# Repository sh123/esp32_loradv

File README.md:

# ESP32 Codec2/OPUS DV Handheld Transceiver

## Introduction
⚠ **Please note that this device is experimental and lacks any form of certification. The author holds no responsibility for any fines incurred due to spectrum misuse, legal violations, or damages caused during its use. As with any experimental project, it is essential that you fully understand what you are doing and use it at your own risk.**

This project is a hobby/amateur/toy/educational radio ESP32 based LoRa/FSK Codec2/OPUS DV 3d printed handheld trasceiver a.k.a. walkie-talkie, which is using 1W/2W `E22-400M30S/E22-400M33S` (SX1268) radio module (UHF, 70cm band) or optionally 100mW `RA-01/RA-02` (SX1278) module. 

In theory, it could also be used with other modules from `E22-xxxMxxS` series with compatible pinouts, but targetting other bands, such as `E22-868M30S/E22-900M30S` (SX1262) modules (UHF, 868/915 MHz) or `E22-170M33S`/`E22-220M30S`, but not tested.

It functions like a standard FM walkie-talkie and, for simplicity and traffic optimization, does not utilize any communication protocol. Instead, it transmits audio codec frames (DV) using pre-configured digital radio modulation, such as LoRA or FSK. There are ideas to add voice over AX.25 and perhaps M17 protocol support in the future.

Overall components cost for this project is about 15-20$.

Schematics for the new board design, which includes integrated components, can be found in the `extras/schematics` directory. The pinouts remain compatible with the first prototype version. While there is a designated space for a GPS module, it should not be soldered as it is not currently supported; it is included solely for potential future experiments.

First prototype is based on https://github.com/sh123/esp32_loraprs modem, but uses additional peripherals:
- I2S speaker module MAX98357A + 4-8ohm 3w speaker (40mm diameter)
- I2S microphone INMP441
- PTT button (new board uses right angeled push button)
- Rotary encoder with push button (new board uses EC11 right angeled encoder)
- Small OLED display SSD1306 128x32
- Battery voltage monitoring (just voltage divider fed into ADC pin, see schematics)
- Powered from a single commonly avaialble 18650 cell (for example from old laptop battery)
- Uses combined charge + 5v boost controller based on Hotchip HT4928S (it is usually used in low capacity single cell USB power banks), but **better to use controllers such as IP5305_SK or similar without auto shutdown on low current!**.

Supports next features:
- Supports LoRa and FSK (no FEC) modulation with configurable modulation parameters from settings
- Supports Codec2 (low bit rate, 700-3200 bps) and OPUS (medium/high bit rate, 2400-512000 bps) audio codecs, codec could be selected from settings
- Goes into ESP32 light sleep when no activity, so all power consumption is around 30-40mA when in sleep RX (even lower with built-in esp32 leds scrapped), wakes up on new data from radio module or when user starts transmitting, consumes about 90-100mA in active receive and about 700-800mA in full power 1W transmit, so single 18650 cell should last for about 48 hours when in idle RX
- Settings menu on long encoder button click, allows to change frequency and other parameters
- Output power tunable from settings from ~1mW (for ISM toy usage) up to 2W (for amateur radio experiments)
- Experimental no warranty privacy option for ISM low power usage (⚠ **check your country regulations if it is allowed by the ISM band plan before experimenting as it might be illegal in some countries**), it is based on [ChaCha20-Poly1305](https://en.wikipedia.org/wiki/ChaCha20-Poly1305) stream cypher provided by [rwheater/Crypto](https://github.com/rweather/arduinolibs) library, it is comparable to AES256, uses 256 bits key, provides message authentication, but should have lower CPU requirements and power usage.

Planned features/ideas:
- Frequency split repeater mode, where two transceivers will be linked using espnow, so one will receive voice on RX frequency and then send packet using espnow to second transmitter which will receive packet using espnow and re-transmit it on TX frequency, this way receiver and transmitter could be positioned further apart with separate antennas thus eliminating need for duplexer
- Bluetooth headset pairing to use with hands free, so can use headset instead of i2s speaker/mic when needed
- Voice over AX.25, so meta data such as callsign could be included and visible on the other end
- M17 protocol support

## Build instructions
- Modify `include/config.h` if needed
- Install platformio
- Build with platformio
- Upload with platformio

## BOM
Bill of materials (BOM) for the new board constuction (credits to n0p and his club members for collecting it)
```
ESP-WROOM32 30pin - https://es.aliexpress.com/item/1005005953505528.html
Modem LoRa E22-400M30S (SX1268) - https://es.aliexpress.com/item/1005003122961059.html
I2S speaker module MAX98357A - https://es.aliexpress.com/item/1005005383121121.html
4ohm 3w speaker (40mm diameter) - https://es.aliexpress.com/item/1005006684947554.html
I2S microphone INMP441 - https://es.aliexpress.com/item/1005007889064664.html
Rotary encoder with push button - https://es.aliexpress.com/item/1005008091948369.html 
Small OLED display SSD1306 128×32 - https://es.aliexpress.com/item/1005008096924594.html
Uses combined charge + 5v boost controller - https://es.aliexpress.com/item/1005008657948784.html

18650 Cell
Botón switch tactile SKHH angled - https://es.aliexpress.com/item/1005005369415986.html
SMA-J-P-X-ST-EM1 Edgemount - https://es.aliexpress.com/item/10000000835065.html
R1 - 100k 0603 - https://es.aliexpress.com/item/1005005677654015.html
R2-R7 - 10k 0603 - https://es.aliexpress.com/item/1005005677654015.html
C1, C3-C8, C10, C11 - 100nF 0603 - https://es.aliexpress.com/item/32371454429.html
C2 - Elec 100uF SMD 3×5,3 - https://es.aliexpress.com/item/1005006724593986.html
C9 - 47uF Radial D4 mm P2 mm - https://es.aliexpress.com/item/1005005022177024.html

GPS - OPTIONAL - UNSUPPORTED ON WALKIE FW - CONFLICTS WITH ON BOARD SERIAL PORT PROGRAMMER - https://es.aliexpress.com/item/1005008733474270.html
```

## Pictures

Two fully 3d printed prototypes were built based on `esp32_loraprs` modem board.

List of peripherals used.

New board design with all components integrated into the board (except battery and charging circuit).

Case for the new board version with battery compartment.

Assembled board with new design.

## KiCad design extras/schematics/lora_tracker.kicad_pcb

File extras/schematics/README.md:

# ESP32 DV transceiver board

This is transceiver board for ESP32 DV handheld transceiver with integrated modules, except battery and charge controller.

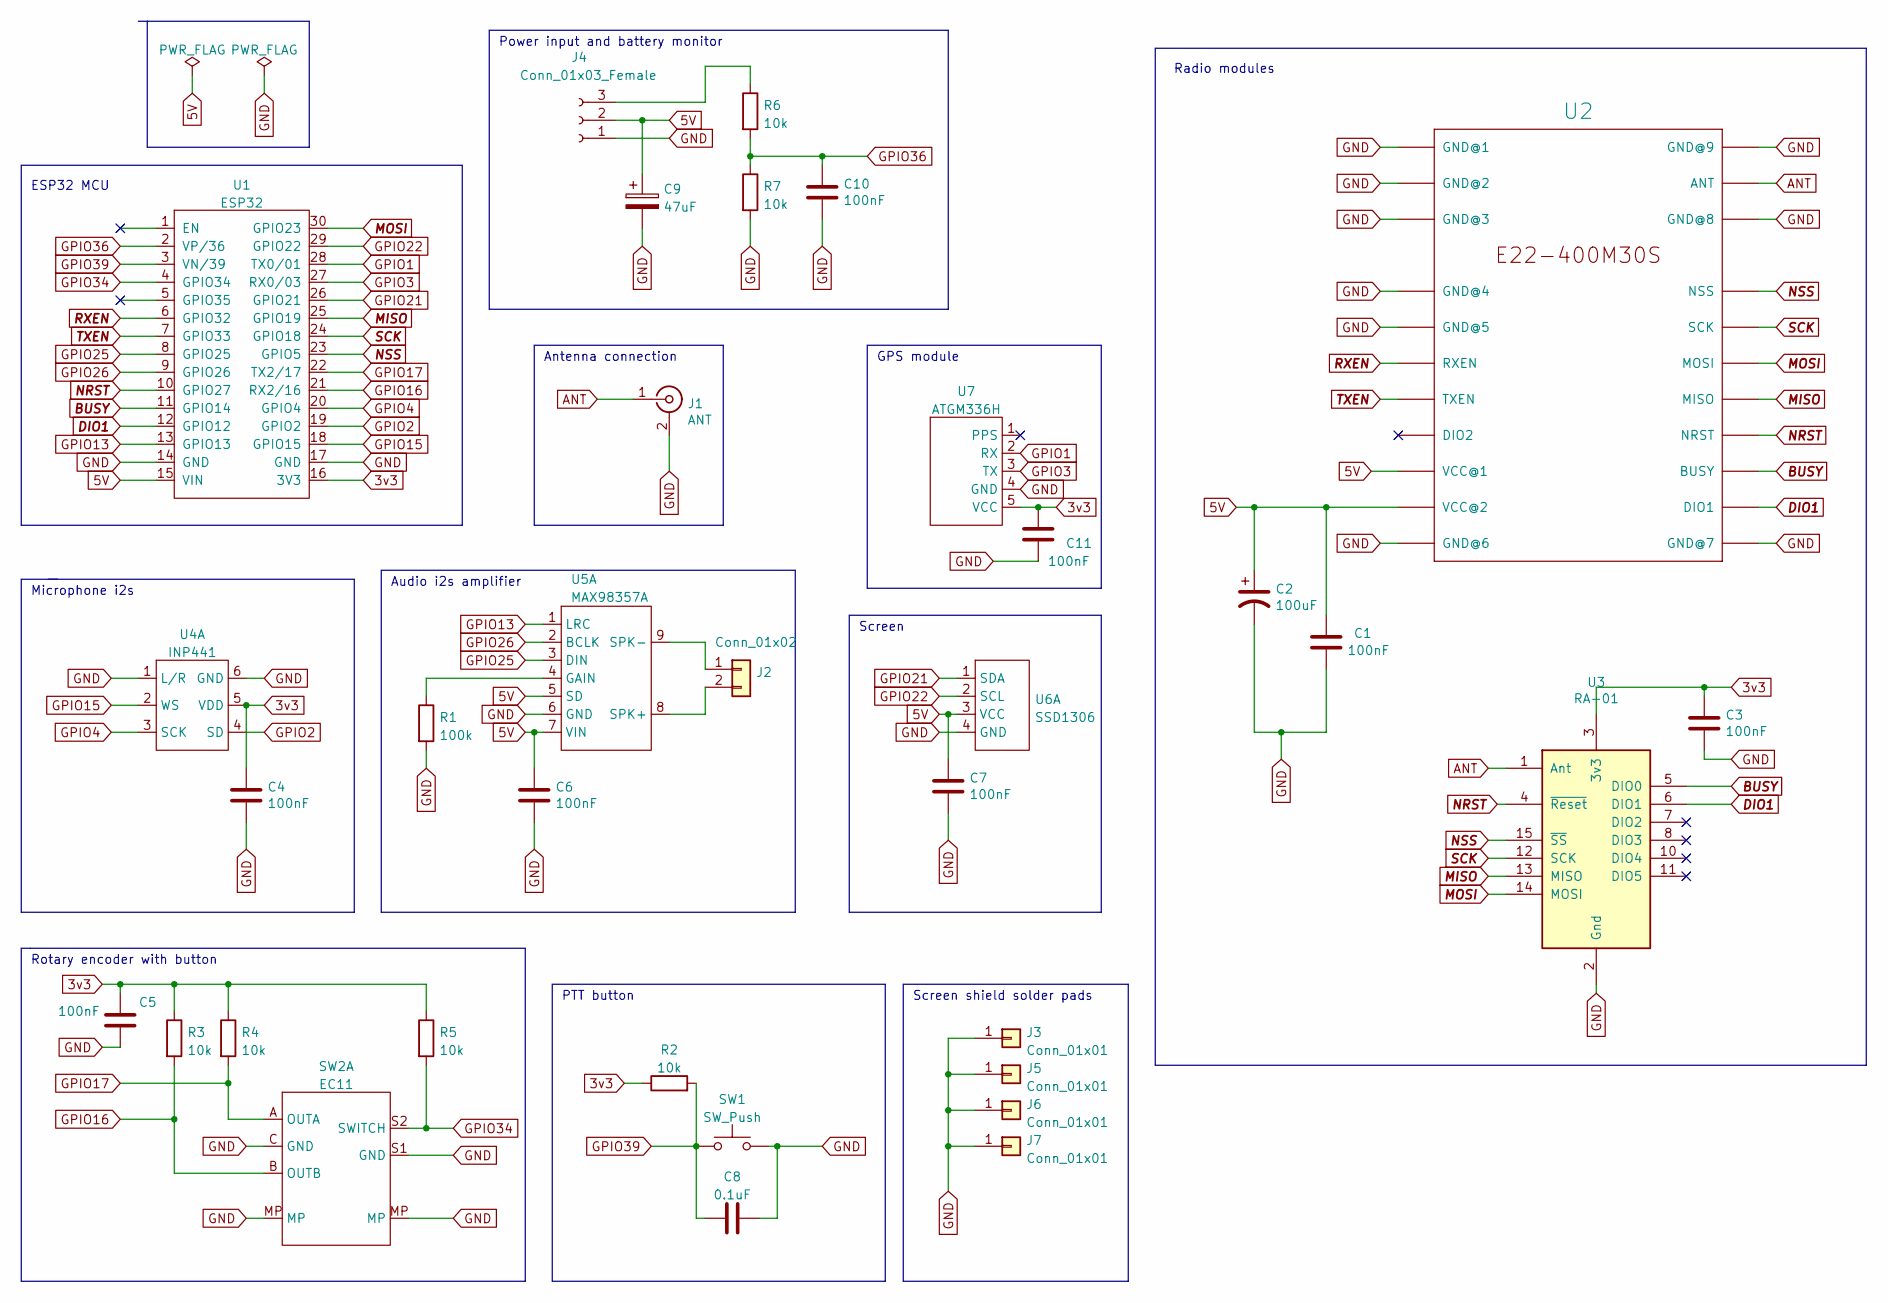
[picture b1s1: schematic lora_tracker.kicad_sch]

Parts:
C1, C3, C4, C5, C6, C7, C10, C11: 100nF; C_0603_1608Metric_Pad1.08x0.95mm_HandSolder
C2: 100uF; CP_Elec_3x5.3
C8: 0.1uF; C_0603_1608Metric_Pad1.08x0.95mm_HandSolder
C9: 47uF; CP_Radial_D4.0mm_P2.00mm
J1: ANT; SMA_Samtec_SMA-J-P-X-ST-EM1_EdgeMount
J2: Conn_01x02; PinHeader_2x01_P2.54mm_Vertical_SMD
J3, J5, J6, J7: Conn_01x01; TestPoint_Pad_1.5x1.5mm
J4: Conn_01x03_Female; PinHeader_1x03_P2.54mm_Vertical
R1: 100k; R_0603_1608Metric_Pad0.98x0.95mm_HandSolder
R2, R3, R4, R5, R6, R7: 10k; R_0603_1608Metric_Pad0.98x0.95mm_HandSolder
SW1: SW_Push; SW_Tactile_SKHH_Angled
SW2: EC11; ec11
U1: ESP32; esp32-devkit-wide_30pin
U2: E22-400M30S
U3: RA-01; Ai-Thinker-Ra-01-LoRa
U4: INP441; inp441
U5: MAX98357A
U6: SSD1306
U7: ATGM336H

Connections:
3v3: C3.1, C4.1, C5.1, C11.1, R2.1, R3.1, R4.1, R5.1, U1.16 (3V3), U3.3 (3v3), U4.5 (VDD), U7.5 (VCC)
5V: C1.1, C2.1, C6.1, C7.1, C9.1, J4.2, U1.15 (VIN), U2.9 (VCC@1), U2.10 (VCC@2), U5.5 (SD), U5.7 (VIN), U6.3 (VCC)
ANT: J1.1 (In), U2.21 (ANT), U3.1 (Ant)
BUSY: U1.11 (GPIO14), U2.14 (BUSY), U3.5 (DIO0)
DIO1: U1.12 (GPIO12), U2.13 (DIO1), U3.6 (DIO1)
GND: C1.2, C2.2, C3.2, C4.2, C5.2, C6.2, C7.2, C8.2, C9.2, C10.2, C11.2, J1.2 (Ext), J3.1, J4.1, J5.1, J6.1, J7.1, R1.2, R7.2, SW1.2, SW2.C (GND), SW2.MP, SW2.S1 (GND), U1.14 (GND), U1.17 (GND), U2.1 (GND@1), U2.2 (GND@2), U2.3 (GND@3), U2.4 (GND@4), U2.5 (GND@5), U2.11 (GND@6), U2.12 (GND@7), U2.20 (GND@8), U2.22 (GND@9), U3.2 (Gnd), U3.9 (Gnd), U3.16 (Gnd), U4.1 (L/R), U4.6 (GND), U5.6 (GND), U6.4 (GND), U7.4 (GND)
GPIO1: U1.28 (TX0/01), U7.2 (RX)
GPIO2: U1.19 (GPIO2), U4.4 (SD)
GPIO3: U1.27 (RX0/03), U7.3 (TX)
GPIO4: U1.20 (GPIO4), U4.3 (SCK)
GPIO13: U1.13 (GPIO13), U5.1 (LRC)
GPIO15: U1.18 (GPIO15), U4.2 (WS)
GPIO16: R3.2, SW2.B (OUTB), U1.21 (RX2/16)
GPIO17: R4.2, SW2.A (OUTA), U1.22 (TX2/17)
GPIO21: U1.26 (GPIO21), U6.1 (SDA)
GPIO22: U1.29 (GPIO22), U6.2 (SCL)
GPIO25: U1.8 (GPIO25), U5.3 (DIN)
GPIO26: U1.9 (GPIO26), U5.2 (BCLK)
GPIO34: R5.2, SW2.S2 (SWITCH), U1.4 (GPIO34)
GPIO36: C10.1, R6.2, R7.1, U1.2 (VP/36)
GPIO39: C8.1, R2.2, SW1.1, U1.3 (VN/39)
MISO: U1.25 (GPIO19), U2.16 (MISO), U3.13 (MISO)
MOSI: U1.30 (GPIO23), U2.17 (MOSI), U3.14 (MOSI)
NRST: U1.10 (GPIO27), U2.15 (NRST), U3.4 (~Reset)
NSS: U1.23 (GPIO5), U2.19 (NSS), U3.15 (~SS)
unnamed: J2.1, U5.9 (SPK-)
unnamed: J2.2, U5.8 (SPK+)
unnamed: J4.3, R6.1
unnamed: R1.1, U5.4 (GAIN)
RXEN: U1.6 (GPIO32), U2.6 (RXEN)
SCK: U1.24 (GPIO18), U2.18 (SCK), U3.12 (SCK)
TXEN: U1.7 (GPIO33), U2.7 (TXEN)

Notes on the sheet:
Antenna connection
Microphone i2s
Audio i2s amplifier
GPS module
Screen shield solder pads
Radio modules
PTT button
Power input and battery monitor
Screen
ESP32 MCU
Rotary encoder with button

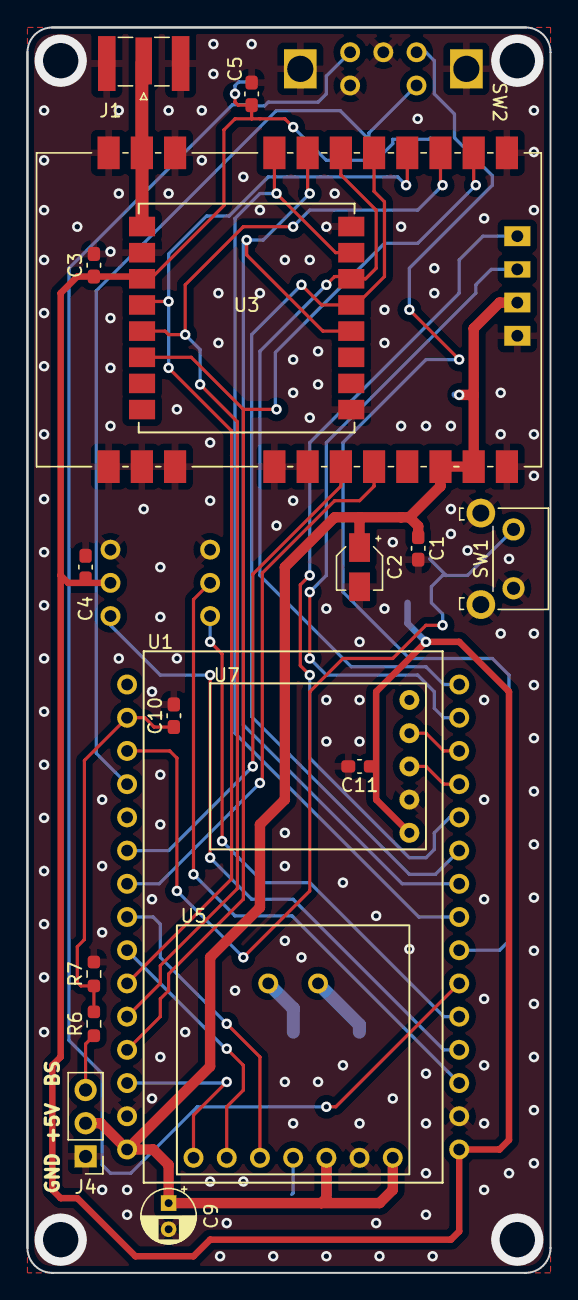
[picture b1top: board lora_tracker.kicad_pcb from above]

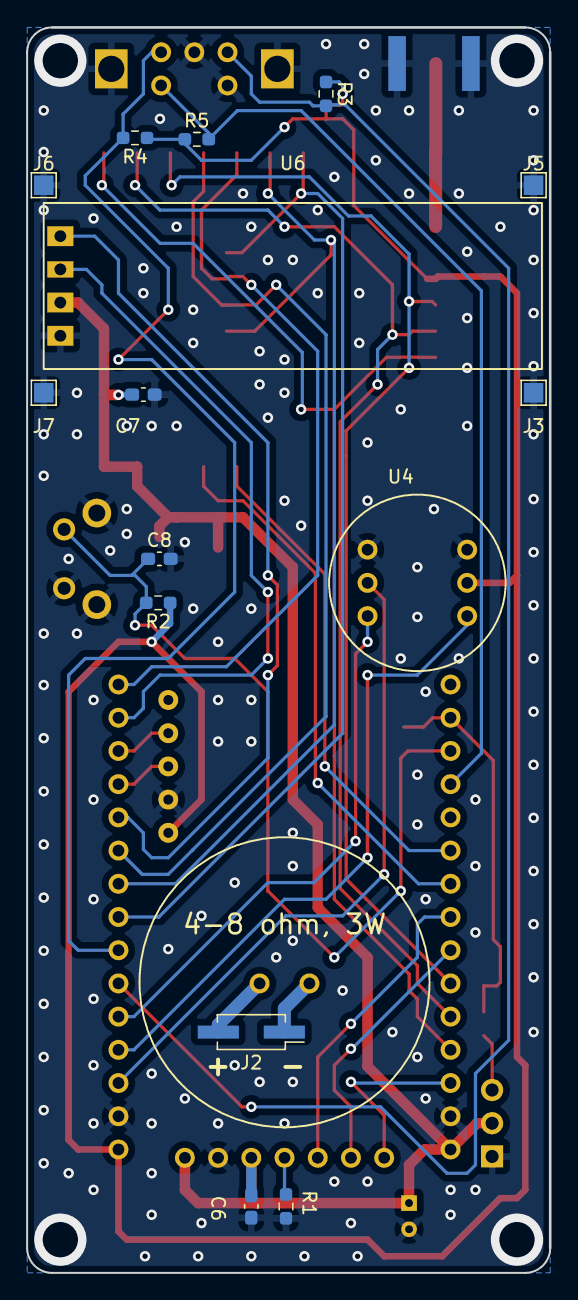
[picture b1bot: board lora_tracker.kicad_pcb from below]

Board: 2 copper layers, 40.0 x 95.2 mm, 34 parts (15 on the bottom side), 32 nets.

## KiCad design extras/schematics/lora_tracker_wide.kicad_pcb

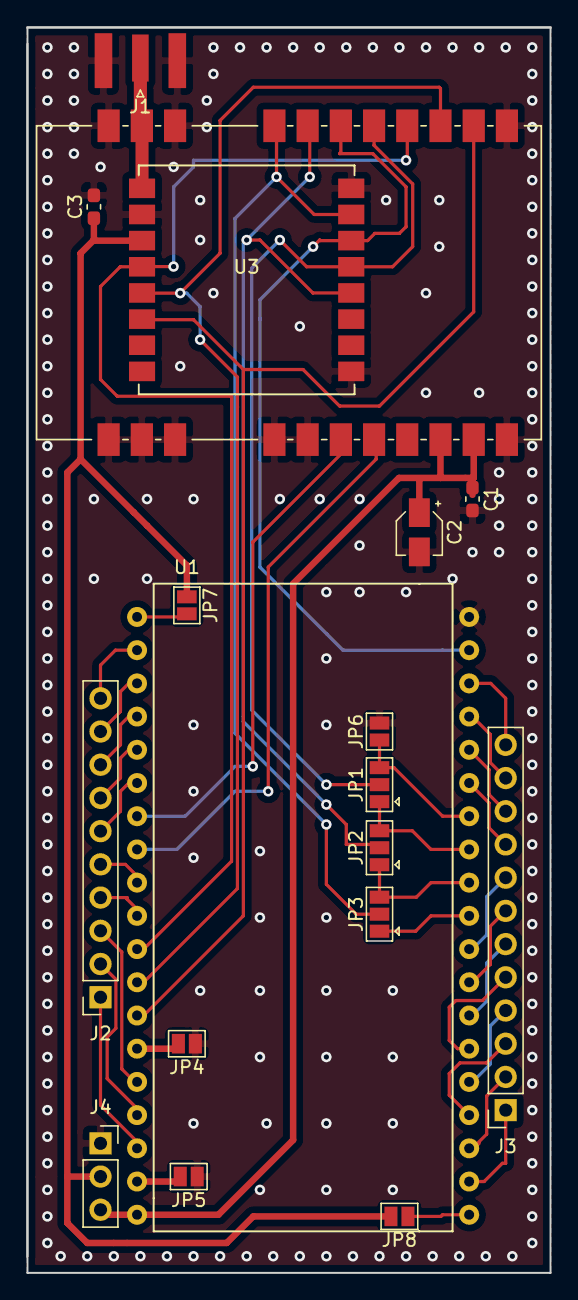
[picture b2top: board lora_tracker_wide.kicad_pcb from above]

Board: 2 copper layers, 40.0 x 95.2 mm, 18 parts (0 on the bottom side), 43 nets.

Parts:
C1, C3: 100nF; C_0603_1608Metric_Pad1.05x0.95mm_HandSolder
C2: 100uF; CP_Elec_3x5.3
J1: Conn_Coaxial; SMA_Samtec_SMA-J-P-H-ST-EM1_EdgeMount
J2: Conn_01x10_Female; PinSocket_1x10_P2.54mm_Vertical
J3: Conn_01x12_Female; PinSocket_1x12_P2.54mm_Vertical
J4: Conn_01x03_Female; PinSocket_1x03_P2.54mm_Vertical
JP1, JP2, JP3: SolderJumper_3_Open; SolderJumper-3_P1.3mm_Open_Pad1.0x1.5mm
JP4, JP5, JP6, JP7, JP8: SolderJumper_2_Open; SolderJumper-2_P1.3mm_Open_Pad1.0x1.5mm
U1: ESP32; esp32-devkit-wide
U2: E22-400M30S
U3: Ai-Thinker-Ra-01; Ai-Thinker-Ra-01-LoRa

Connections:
3v3: C3.1, J4.2, JP7.1, JP8.2, U3.3
BUSY: U1.12, U2.14, U3.5
DIO1: U1.13, U2.13, U3.6
EN: J2.10, U1.2
GND: C1.2, C2.2, C3.2, J1.2, J4.1, JP4.1, JP5.1, JP6.2, U1.38, U2.1, U2.2, U2.3, U2.4, U2.5, U2.11, U2.12, U2.20, U2.22, U3.2, U3.9, U3.16
GPIO0: J3.5, U1.25
GPIO1: J3.11, U1.35
GPIO2: J3.4, U1.24
GPIO3: J3.10, U1.34
GPIO4: J3.6, U1.26
GPIO7: J3.1, U1.21
GPIO8: J3.2, U1.22
GPIO9: J2.2, U1.16
GPIO10: J2.1, U1.17
GPIO13: J2.3, U1.15
GPIO15: J3.3, U1.23
GPIO16: J3.7, U1.27
GPIO17: J3.8, U1.28
GPIO21: J3.9, U1.33
GPIO22: J3.12, U1.36
GPIO25: J2.5, U1.9
GPIO26: J2.4, U1.10
GPIO34: J2.7, U1.5
GPIO35: J2.6, U1.6
GPIO36: J2.9, U1.3
GPIO39: J2.8, U1.4
MISO: JP1.2, U2.16, U3.13
MOSI: U1.37, U2.17, U3.14
NRST: U1.11, U2.15, U3.4
NSS: JP3.2, U2.19, U3.15
unnamed: J1.1, U2.21, U3.1
unnamed: JP1.1, JP2.3, U1.31
unnamed: JP1.3, JP6.1, U1.32
unnamed: JP2.1, JP3.3, U1.30
unnamed: JP3.1, U1.29
unnamed: JP4.2, U1.14
unnamed: JP5.2, U1.18
unnamed: JP7.2, U1.1
unnamed: JP8.1, U1.20
RXEN: U1.7, U2.6
SCK: JP2.2, U2.18, U3.12
TXEN: U1.8, U2.7
VCC: C1.1, C2.1, J4.3, U1.19, U2.9, U2.10

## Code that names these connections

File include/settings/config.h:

#ifndef LORADV_CONFIG_H
#define LORADV_CONFIG_H

#include <Arduino.h>
#include <Preferences.h>

#define DEBUGLOG_DEFAULT_LOG_LEVEL_INFO
#include <DebugLog.h>

#include "version.h"
#include "settings/default_config.h"

namespace LoraDv {

class Config {
public:
  int Version;          // config version

  DebugLogLevel LogLevel;    // log level

  // modulation type
  int ModType;          // 0 - lora, 1 - fsk

  // lora modulation parameters
  long LoraFreqRx;      // lora RX frequency, e.g. 433.775e6
  long LoraFreqTx;      // lora TX frequency, e.g. 433.775e6
  long LoraFreqStep;    // lora frequency step
  long LoraBw;          // lora bandwidth, e.g. 125e3
  int LoraSf;           // lora spreading factor, e.g. 12
  int LoraCodingRate;   // lora coding rate, e.g. 7
  int LoraPower;        // lora power level in dbm, 20
  int LoraSync_;        // lora sync word/packet id, 0x34
  int LoraCrc_;         // lora crc mode, 0 - disabled, 1 - 1 byte, 2 - 2 bytes
  int LoraPreambleLen_; // lora preamble length from 6 to 65535

  // fsk modulation parameters
  float FskBitRate;     // fsk bit rate, 0.6 - 300.0 Kbps
  float FskFreqDev;     // fsk frequency deviation 0.6 - 200 kHz
  float FskRxBw;        // fsk rx bandwidth, discrete from 4.8 to 467 kHz
  byte FskShaping;      // fsk gaussian shaping

  // lora hardware pinouts and isr
  byte LoraPinSs_;       // lora ss pin
  byte LoraPinRst_;      // lora rst pin
  byte LoraPinA_;        // (sx127x - dio0, sx126x/sx128x - dio1)
  byte LoraPinB_;        // (sx127x - dio1, sx126x/sx128x - busy)
  byte LoraPinSwitchRx_; // (sx127x - unused, sx126x - RXEN pin number)
  byte LoraPinSwitchTx_; // (sx127x - unused, sx126x - TXEN pin number)
  long LoraFreqMin_;     // module minimum frequency
  long LoraFreqMax_;     // module maximum frequency
  
  // rotary encoder
  byte EncoderPinA_;     // Encoder A pin number
  byte EncoderPinB_;     // Encoder B pin number
  byte EncoderPinBtn_;   // Encoder button pin number
  byte EncoderPinVcc_;   // Encoder VCC pin (or -1 if not connected)
  byte EncoderSteps_;    // Encoder number of steps

  // audio params
  int AudioCodec;         // type of audio codec, 0 - Codec2, 1 - OPUS
  int AudioResampleCoeff_; // resample coefficient when audio rate is not equal code rate
  uint32_t AudioSampleRate_; // sample rate for mic and speaker
  uint32_t AudioCodecSampleRate_; // sammple rate for codec
  int AudioHpfCutoffHz_;  // high pass fitler cutoff frequency

  // codec2
  int AudioCodec2Mode;   // Audio Codec2 mode
  int AudioMaxPktSize;   // Aggregated packet maximum size

  // audio opus
  int AudioOpusRate;  // opus bit rate 2.4 - 512 kbps
  float AudioOpusPcmLen;   // opus pcm frame length, 2.5, 5, 10, 20, 40, 60, 80, 100, 120 ms  

  // i2s speaker
  byte AudioSpkPinBclk_; // Speaker i2s clk pin
  byte AudioSpkPinLrc_;  // Speaker i2s lrc pin
  byte AudioSpkPinDin_;  // Speaker i2s din pin

  // i2s mic
  byte AudioMicPinSd_;   // Mic i2s sd pin
  byte AudioMicPinWs_;   // Mic i2s ws pin
  byte AudioMicPinSck_;  // Mic i2s sck pin

  // audio state
  int AudioMaxVol_;      // maximum volume
  int AudioVol;          // current volume

  // privacy
  bool AudioEnPriv;     // enable/disable privacy
  byte AudioPrivacyKey_[32]; // privacy key

  // battery monitor
  byte BatteryMonPin_;   // Battery monitor adc pin
  float BatteryMonCal;   // Battery monitor calibrarion value

  // power management
  int PmSleepAfterMs; // Light sleep activation after given ms
  int PmLightSleepDurationMs_; // How long to sleep
  int PmLightSleepAwakeMs_; // How long to be active

  // ptt button
  int PttBtnPin_;            // ptt pin

public:
  Config();
  void Load();
  void Save();
  void Reset();

private:
  void InitializeDefault();

  Preferences prefs_;

}; // Config

} // LoraDv

#endif // LORADV_CONFIG_H

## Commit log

2022-12-19 Update config
2022-12-19 Config update
2022-12-19 Fix pointer
2022-12-19 Fixes
2022-12-19 Cleanup
2022-12-20 Refactoring
2022-12-21 Remove unused declaration
2022-12-22 Frequency formatting
2022-12-22 Store volume in settings
2022-12-22 Refactor
2022-12-22 Support for half duplex operation
2022-12-22 Task temination
2022-12-22 Simplify config
2022-12-22 Persistent settings
2022-12-22 Added missing file
2022-12-23 Added one more image
2022-12-24 Refactor setup
2022-12-24 Added freq tep into config
2022-12-24 Refactor volume
2022-12-24 Menu items
2022-12-24 Settings menu
2022-12-24 Menu fixes
2022-12-24 Save-reset settings menu
2022-12-24 Reboot settings
2022-12-24 Info settings
2022-12-24 Cosmetic fixes
2022-12-25 More info
2022-12-28 Main screen status changes
2022-12-28 Show rssi and wait/rx status
2023-03-01 Add radiolib include into the config.h
2023-03-03 Fix compilation for sx127x
2023-03-15 Set preamble length from config
2023-03-15 Update version
2023-03-15 Update confiig
2023-03-15 Update libraries
2023-11-12 Logging
2023-11-12 Increase espressif version
2023-11-12 Increase version
2023-11-13 Consume latest version of codec2
2023-11-14 Increase maximum volume and update rx/tx logic
2023-11-14 Remove implicit header usage
2023-11-15 Add support for fsk
2023-11-15 Add missing menu
2023-11-15 Update menu
2023-11-15 Updated default settings for fsk
2023-11-17 Make maximum packet size modifiable from settigns
2023-11-20 Add settings option to set FSK shaping
2023-12-02 Fix compilation issue for SX127x
2023-12-04 Add experimental privacy option
2023-12-15 Added codec interface
2023-12-15 Update some start declarations
2023-12-16 Added OPUS settings
2023-12-16 Codec2/OPUS selection
2023-12-16 Reorder settings
2023-12-16 Renames
2023-12-16 API to get buffer sizes
2023-12-16 Initialization
2023-12-16 Codec selection
2023-12-17 Codec updates
2023-12-17 Pcm length fixes
2023-12-17 Better tx logic
2024-10-26 Add option to operate i2s peripherals at 16000 and resample to codec's 8000
2024-10-26 Improve upsampling
2024-10-26 Decrease polling delay
2024-10-28 Adjust maximum volume
2024-10-28 Improve light sleep
2024-10-28 Code formatting
2024-10-29 Update radiolib and espressif32
2024-10-29 Update circular buffer, SSD1306 and encoder libraries
2024-10-29 Redesign volume and add AGC for playback
2024-10-29 Updated version
2024-10-30 Added schematics
2024-10-30 Migrated libraries to kicad_sym
2024-10-30 Add missing files
2024-10-30 Updated esp32 symbol
2024-10-30 Update schematics
2024-10-31 Updated schematics
2024-11-01 Added models
2024-11-02 Comments
2024-11-16 Added gerber
2024-11-16 Removed old files
2024-11-16 Added gerber files
2024-11-16 Added image
2024-12-23 Added empty models
2024-12-24 Update base model
2024-12-24 Update model
2024-12-24 Update main model
2024-12-25 Update image
2024-12-25 Add image
2024-12-26 Update models
2024-12-26 Added knob
2024-12-29 Updated battery compartment model
2024-12-30 Added upper cover with no battery compartment
2024-12-30 Added antenna models
2024-12-31 Battery lid
2025-01-02 Pin audio and radio tasks to separate cores
2025-01-04 Automatic restart after saving settings
2025-03-16 Restart esp after saving settings
2025-03-30 Refactor to subdirectories
2025-03-30 Refactor settings and config into subfolders
2025-03-30 Refactor into subdirectories
2025-03-30 Upgrade espressif to latest version
2025-04-06 Logarithmic volume control for better perception
2025-04-06 Adjust multiplier
2025-04-11 Refactoring logging
2025-04-28 Add de-allocation of one of buffers
2025-05-01 Implement ChaChaPoly
2025-05-01 Change trace level
2025-05-02 Remove unused statment
2025-05-02 Fix wrong boundary
2025-05-02 Use esp built-in RNG number generator for IV generation
2025-06-08 Increase IV/nonce size from 8 to 12 bytes to be compatible with other libraries
2025-06-08 Remove need for additional tag data
2025-12-18 Update libraries and fix issue with receiving
2025-12-19 Change default parameters and set HPF fitler frequency to 300 Hz
2025-12-19 Update power consumption details in README
    Added estimated battery life for idle RX with a single 18650 cell.
2025-12-24 Fix typo in README regarding battery life
2026-01-04 Do not wake on BUSY line, only on DIO1
2026-01-04 Power management optiizations
2026-01-04 Revise power controller recommendation in README
    Updated information about the power controller recommendation.
2026-01-06 Improve logging
2026-01-06 Upgrade codec2 lib
2026-01-07 Limit maximum bit rate for opus in settings up to 16000 bps
2026-01-11 Refactor defautl settings into variant files
2026-01-28 Do not make power management optimizations, add separate platformio target for that
2026-01-29 Added varian file for 868 module
2026-01-29 Update values
2026-02-02 Do not set suffix sx1268 by default for variant files
2026-02-28 Fix bug in variant file
